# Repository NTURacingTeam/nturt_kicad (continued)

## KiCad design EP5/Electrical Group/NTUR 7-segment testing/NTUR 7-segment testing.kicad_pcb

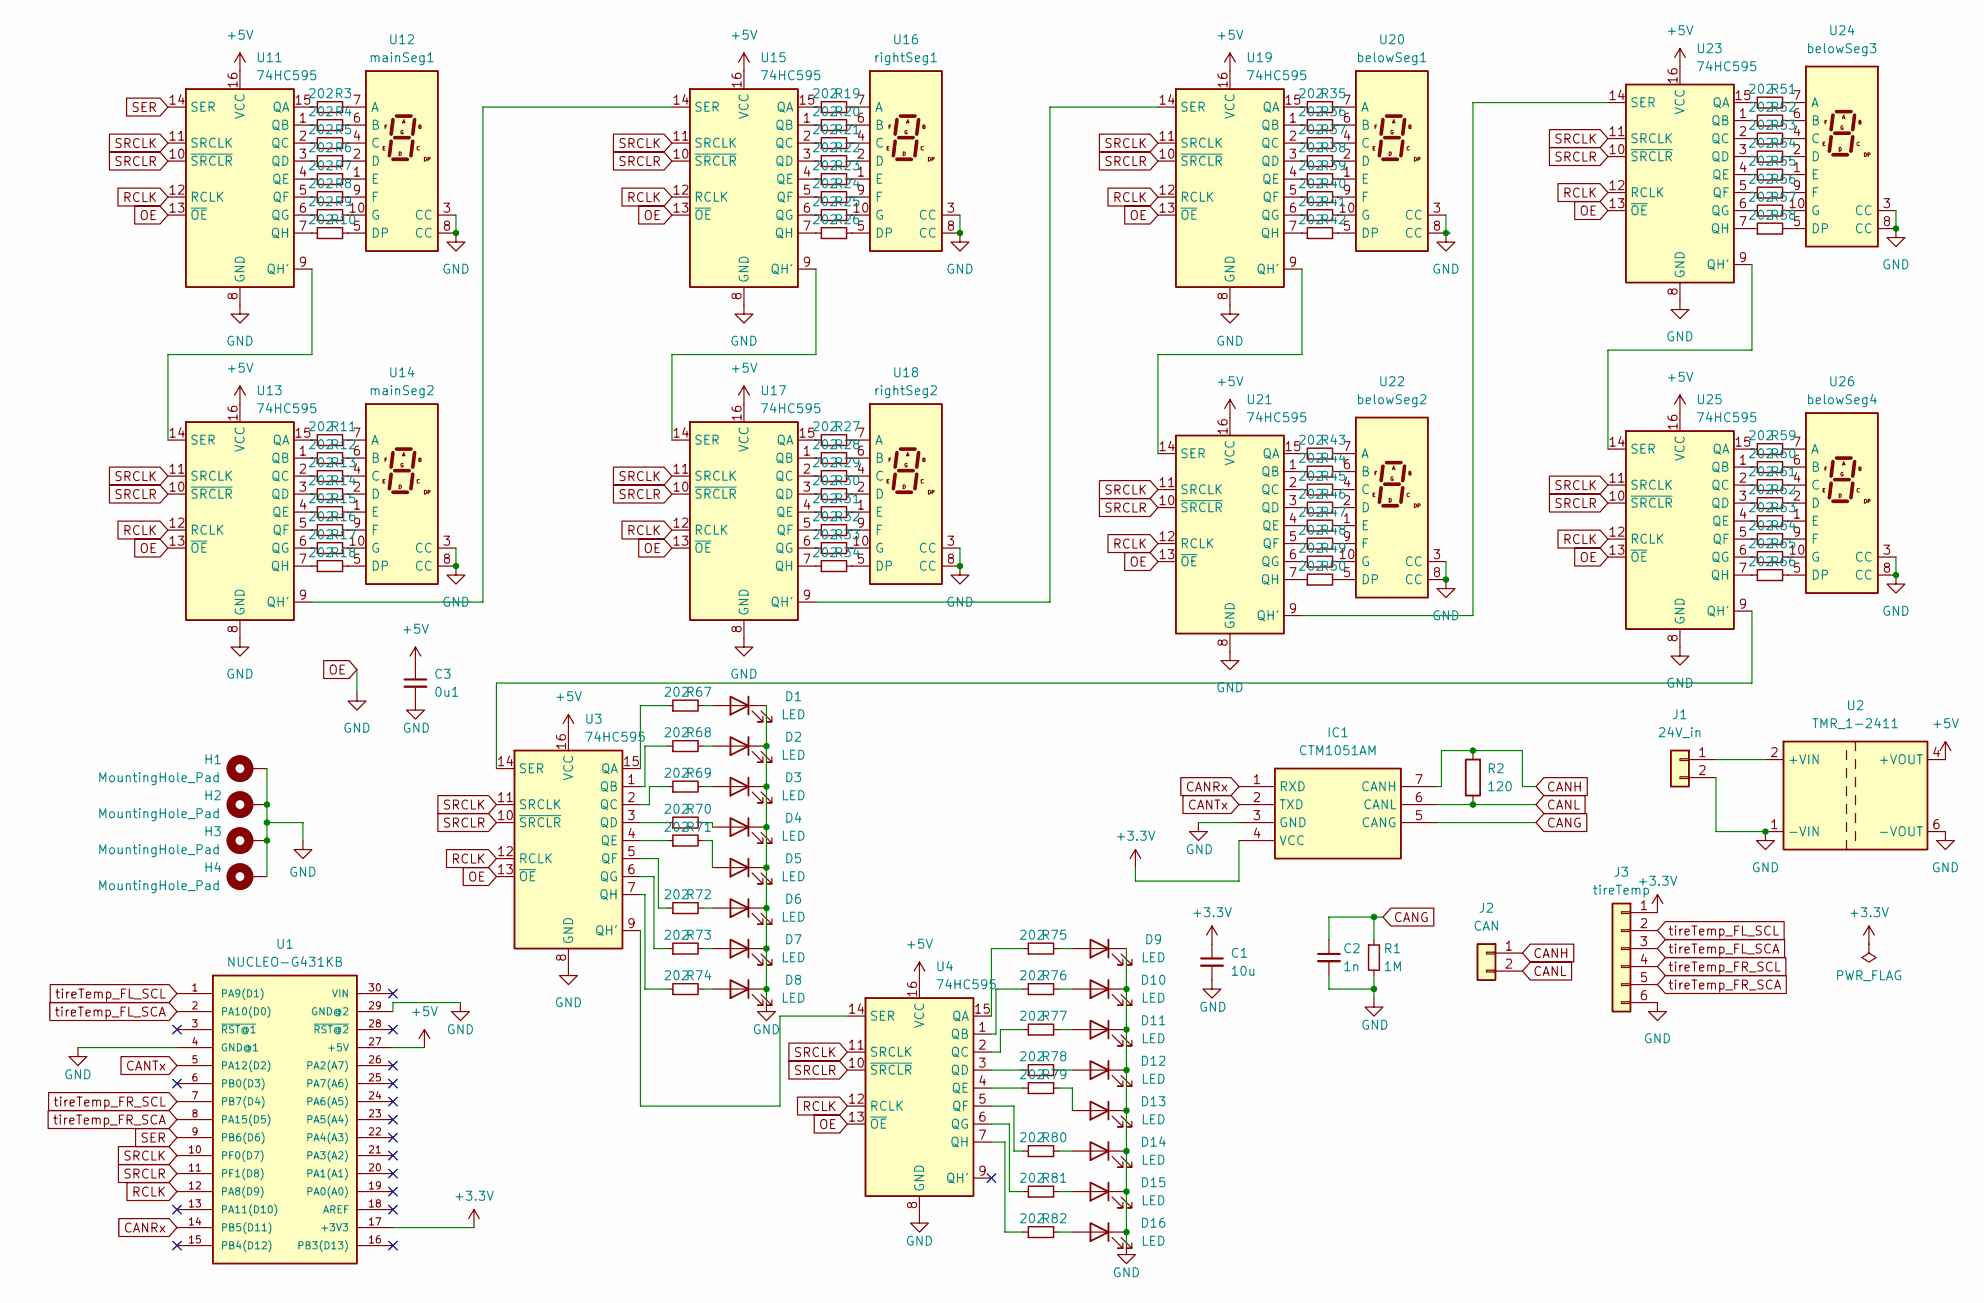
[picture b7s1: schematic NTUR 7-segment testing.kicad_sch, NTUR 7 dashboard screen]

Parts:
C1: 10u; C_0805_2012Metric_Pad1.18x1.45mm_HandSolder
C2: 1n; C_Disc_D5.0mm_W2.5mm_P5.00mm
C3: 0u1; C_0805_2012Metric_Pad1.18x1.45mm_HandSolder
D1, D2, D3, D4, D5, D6, D7, D8, D9, D10, D11, D12, D13, D14, D15, D16: LED; LED_1812_4532Metric
H1, H2, H3, H4: MountingHole_Pad; MountingHole_2.2mm_M2_DIN965_Pad_TopBottom
IC1: CTM1051AM; Manufacturer_Part_Number CTM1051AM
J1: 24V_in; JST_XH_S2B-XH-A-1_1x02_P2.50mm_Horizontal
J2: CAN; JST_XH_S2B-XH-A-1_1x02_P2.50mm_Horizontal
J3: tireTemp; JST_XH_S6B-XH-A-1_1x06_P2.50mm_Horizontal
R1: 1M; R_0603_1608Metric
R2: 120; R_1206_3216Metric
R3, R4, R5, R6, R7, R8, R9, R10, R11, R12, R13, R14, R15, R16, R17, R18, R19, R20, R21, R22, R23, R24, R25, R26, R27, R28, R29, R30, R31, R32, R33, R34, R35, R36, R37, R38, R39, R40, R41, R42, R43, R44, R45, R46, R47, R48, R49, R50, R51, R52, R53, R54, R55, R56, R57, R58, R59, R60, R61, R62, R63, R64, R65, R66, R67, R68, R69, R70, R71, R72, R73, R74, R75, R76, R77, R78, R79, R80, R81, R82: 202; R_0805_2012Metric
U1: NUCLEO-G431KB; MANUFACTURER_PART_NUMBER NUCLEO-F303K8
U2: TMR_1-2411; Converter_DCDC_TRACO_TMR-1-xxxx_Single_THT
U3, U4, U11, U13, U15, U17, U19, U21, U23, U25: 74HC595; DIP-16_W7.62mm_Socket_LongPads
U12: mainSeg1; 1digit 7 segment display 1.5inch
U14: mainSeg2; 1digit 7 segment display 1.5inch
U16: rightSeg1; 1digit 7 segment display 0.56inch
U18: rightSeg2; 1digit 7 segment display 0.56inch
U20: belowSeg1; 1digit 7 segment display 0.56inch
U22: belowSeg2; 1digit 7 segment display 0.56inch
U24: belowSeg3; 1digit 7 segment display 0.56inch
U26: belowSeg4; 1digit 7 segment display 0.56inch

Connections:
+3.3V: C1.1, IC1.4 (VCC), J3.1, U1.17 (+3V3)
+5V: C3.1, U1.27 (+5V), U2.4 (+VOUT), U3.16 (VCC), U4.16 (VCC), U11.16 (VCC), U13.16 (VCC), U15.16 (VCC), U17.16 (VCC), U19.16 (VCC), U21.16 (VCC), U23.16 (VCC), U25.16 (VCC)
CANG: C2.1, IC1.5 (CANG), R1.1
CANH: IC1.7 (CANH), J2.1, R2.2
CANL: IC1.6 (CANL), J2.2, R2.1
CANRx: IC1.1 (RXD), U1.14 (PB5(D11))
CANTx: IC1.2 (TXD), U1.5 (PA12(D2))
unnamed: D1.2 (A), R67.2
unnamed: D2.2 (A), R68.2
unnamed: D3.2 (A), R69.2
unnamed: D4.2 (A), R70.2
unnamed: D5.2 (A), R71.2
unnamed: D6.2 (A), R72.2
unnamed: D7.2 (A), R73.2
unnamed: D8.2 (A), R74.2
unnamed: D9.2 (A), R75.2
unnamed: D10.2 (A), R76.2
unnamed: D11.2 (A), R77.2
unnamed: D12.2 (A), R78.2
unnamed: D13.2 (A), R79.2
unnamed: D14.2 (A), R80.2
unnamed: D15.2 (A), R81.2
unnamed: D16.2 (A), R82.2
unnamed: J1.1, U2.2 (+VIN)
unnamed: R67.1, U3.15 (QA)
unnamed: R68.1, U3.1 (QB)
unnamed: R69.1, U3.2 (QC)
unnamed: R70.1, U3.3 (QD)
unnamed: R71.1, U3.4 (QE)
unnamed: R72.1, U3.5 (QF)
unnamed: R73.1, U3.6 (QG)
unnamed: U3.9 (QH'), U4.14 (SER)
unnamed: R74.1, U3.7 (QH)
unnamed: R75.1, U4.15 (QA)
unnamed: R76.1, U4.1 (QB)
unnamed: R77.1, U4.2 (QC)
unnamed: R78.1, U4.3 (QD)
unnamed: R79.1, U4.4 (QE)
unnamed: R80.1, U4.5 (QF)
unnamed: R81.1, U4.6 (QG)
unnamed: R82.1, U4.7 (QH)
unnamed: R3.1, U11.15 (QA)
unnamed: R4.1, U11.1 (QB)
unnamed: R5.1, U11.2 (QC)
unnamed: R6.1, U11.3 (QD)
unnamed: R7.1, U11.4 (QE)
unnamed: R8.1, U11.5 (QF)
unnamed: R9.1, U11.6 (QG)
unnamed: U11.9 (QH'), U13.14 (SER)
unnamed: R10.1, U11.7 (QH)
unnamed: R3.2, U12.7 (A)
unnamed: R4.2, U12.6 (B)
unnamed: R5.2, U12.4 (C)
unnamed: R6.2, U12.2 (D)
unnamed: R10.2, U12.5 (DP)
unnamed: R7.2, U12.1 (E)
unnamed: R8.2, U12.9 (F)
unnamed: R9.2, U12.10 (G)
unnamed: R11.1, U13.15 (QA)
unnamed: R12.1, U13.1 (QB)
unnamed: R13.1, U13.2 (QC)
unnamed: R14.1, U13.3 (QD)
unnamed: R15.1, U13.4 (QE)
unnamed: R16.1, U13.5 (QF)
unnamed: R17.1, U13.6 (QG)
unnamed: U13.9 (QH'), U15.14 (SER)
unnamed: R18.1, U13.7 (QH)
unnamed: R11.2, U14.7 (A)
unnamed: R12.2, U14.6 (B)
unnamed: R13.2, U14.4 (C)
unnamed: R14.2, U14.2 (D)
unnamed: R18.2, U14.5 (DP)
unnamed: R15.2, U14.1 (E)
unnamed: R16.2, U14.9 (F)
unnamed: R17.2, U14.10 (G)
unnamed: R19.1, U15.15 (QA)
unnamed: R20.1, U15.1 (QB)
unnamed: R21.1, U15.2 (QC)
unnamed: R22.1, U15.3 (QD)
unnamed: R23.1, U15.4 (QE)
unnamed: R24.1, U15.5 (QF)
unnamed: R25.1, U15.6 (QG)
unnamed: U15.9 (QH'), U17.14 (SER)
unnamed: R26.1, U15.7 (QH)
unnamed: R19.2, U16.7 (A)
unnamed: R20.2, U16.6 (B)
unnamed: R21.2, U16.4 (C)
unnamed: R22.2, U16.2 (D)
unnamed: R26.2, U16.5 (DP)
unnamed: R23.2, U16.1 (E)
unnamed: R24.2, U16.9 (F)
unnamed: R25.2, U16.10 (G)
unnamed: R27.1, U17.15 (QA)
unnamed: R28.1, U17.1 (QB)
unnamed: R29.1, U17.2 (QC)
unnamed: R30.1, U17.3 (QD)
unnamed: R31.1, U17.4 (QE)
unnamed: R32.1, U17.5 (QF)
unnamed: R33.1, U17.6 (QG)
unnamed: U17.9 (QH'), U19.14 (SER)
unnamed: R34.1, U17.7 (QH)
unnamed: R27.2, U18.7 (A)
unnamed: R28.2, U18.6 (B)
unnamed: R29.2, U18.4 (C)
unnamed: R30.2, U18.2 (D)
unnamed: R34.2, U18.5 (DP)
unnamed: R31.2, U18.1 (E)
unnamed: R32.2, U18.9 (F)
unnamed: R33.2, U18.10 (G)
unnamed: R35.1, U19.15 (QA)
unnamed: R36.1, U19.1 (QB)
unnamed: R37.1, U19.2 (QC)
unnamed: R38.1, U19.3 (QD)
unnamed: R39.1, U19.4 (QE)
unnamed: R40.1, U19.5 (QF)
unnamed: R41.1, U19.6 (QG)
unnamed: U19.9 (QH'), U21.14 (SER)
unnamed: R42.1, U19.7 (QH)
unnamed: R35.2, U20.7 (A)
unnamed: R36.2, U20.6 (B)
unnamed: R37.2, U20.4 (C)
unnamed: R38.2, U20.2 (D)
unnamed: R42.2, U20.5 (DP)
unnamed: R39.2, U20.1 (E)
unnamed: R40.2, U20.9 (F)
unnamed: R41.2, U20.10 (G)
unnamed: R43.1, U21.15 (QA)
unnamed: R44.1, U21.1 (QB)
unnamed: R45.1, U21.2 (QC)
unnamed: R46.1, U21.3 (QD)
unnamed: R47.1, U21.4 (QE)
unnamed: R48.1, U21.5 (QF)
unnamed: R49.1, U21.6 (QG)
unnamed: U21.9 (QH'), U23.14 (SER)
unnamed: R50.1, U21.7 (QH)
unnamed: R43.2, U22.7 (A)
unnamed: R44.2, U22.6 (B)
unnamed: R45.2, U22.4 (C)
unnamed: R46.2, U22.2 (D)
unnamed: R50.2, U22.5 (DP)
unnamed: R47.2, U22.1 (E)
unnamed: R48.2, U22.9 (F)
unnamed: R49.2, U22.10 (G)
unnamed: R51.1, U23.15 (QA)
unnamed: R52.1, U23.1 (QB)
unnamed: R53.1, U23.2 (QC)
unnamed: R54.1, U23.3 (QD)
unnamed: R55.1, U23.4 (QE)
unnamed: R56.1, U23.5 (QF)
unnamed: R57.1, U23.6 (QG)
unnamed: U23.9 (QH'), U25.14 (SER)
unnamed: R58.1, U23.7 (QH)
unnamed: R51.2, U24.7 (A)
unnamed: R52.2, U24.6 (B)
unnamed: R53.2, U24.4 (C)
unnamed: R54.2, U24.2 (D)
unnamed: R58.2, U24.5 (DP)
unnamed: R55.2, U24.1 (E)
unnamed: R56.2, U24.9 (F)
unnamed: R57.2, U24.10 (G)
unnamed: R59.1, U25.15 (QA)
unnamed: R60.1, U25.1 (QB)
unnamed: R61.1, U25.2 (QC)
unnamed: R62.1, U25.3 (QD)
unnamed: R63.1, U25.4 (QE)
unnamed: R64.1, U25.5 (QF)
unnamed: R65.1, U25.6 (QG)
unnamed: U3.14 (SER), U25.9 (QH')
unnamed: R66.1, U25.7 (QH)
unnamed: R59.2, U26.7 (A)
unnamed: R60.2, U26.6 (B)
unnamed: R61.2, U26.4 (C)
unnamed: R62.2, U26.2 (D)
unnamed: R66.2, U26.5 (DP)
unnamed: R63.2, U26.1 (E)
unnamed: R64.2, U26.9 (F)
unnamed: R65.2, U26.10 (G)
OE: C1.2, C2.2, C3.2, D1.1 (K), D2.1 (K), D3.1 (K), D4.1 (K), D5.1 (K), D6.1 (K), D7.1 (K), D8.1 (K), D9.1 (K), D10.1 (K), D11.1 (K), D12.1 (K), D13.1 (K), D14.1 (K), D15.1 (K), D16.1 (K), H1.1, H2.1, H3.1, H4.1, IC1.3 (GND), J1.2, J3.6, R1.2, U1.4 (GND@1), U1.29 (GND@2), U2.1 (-VIN), U2.6 (-VOUT), U3.8 (GND), U3.13 (~OE), U4.8 (GND), U4.13 (~OE), U11.8 (GND), U11.13 (~OE), U12.3 (CC), U12.8 (CC), U13.8 (GND), U13.13 (~OE), U14.3 (CC), U14.8 (CC), U15.8 (GND), U15.13 (~OE), U16.3 (CC), U16.8 (CC), U17.8 (GND), U17.13 (~OE), U18.3 (CC), U18.8 (CC), U19.8 (GND), U19.13 (~OE), U20.3 (CC), U20.8 (CC), U21.8 (GND), U21.13 (~OE), U22.3 (CC), U22.8 (CC), U23.8 (GND), U23.13 (~OE), U24.3 (CC), U24.8 (CC), U25.8 (GND), U25.13 (~OE), U26.3 (CC), U26.8 (CC)
RCLK: U1.12 (PA8(D9)), U3.12 (RCLK), U4.12 (RCLK), U11.12 (RCLK), U13.12 (RCLK), U15.12 (RCLK), U17.12 (RCLK), U19.12 (RCLK), U21.12 (RCLK), U23.12 (RCLK), U25.12 (RCLK)
SER: U1.9 (PB6(D6)), U11.14 (SER)
SRCLK: U1.10 (PF0(D7)), U3.11 (SRCLK), U4.11 (SRCLK), U11.11 (SRCLK), U13.11 (SRCLK), U15.11 (SRCLK), U17.11 (SRCLK), U19.11 (SRCLK), U21.11 (SRCLK), U23.11 (SRCLK), U25.11 (SRCLK)
SRCLR: U1.11 (PF1(D8)), U3.10 (~SRCLR), U4.10 (~SRCLR), U11.10 (~SRCLR), U13.10 (~SRCLR), U15.10 (~SRCLR), U17.10 (~SRCLR), U19.10 (~SRCLR), U21.10 (~SRCLR), U23.10 (~SRCLR), U25.10 (~SRCLR)
tireTemp_FL_SCA: J3.3, U1.2 (PA10(D0))
tireTemp_FL_SCL: J3.2, U1.1 (PA9(D1))
tireTemp_FR_SCA: J3.5, U1.8 (PA15(D5))
tireTemp_FR_SCL: J3.4, U1.7 (PB7(D4))

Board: 2 copper layers, 129 parts (25 on the bottom side), 186 nets, no tracks yet.

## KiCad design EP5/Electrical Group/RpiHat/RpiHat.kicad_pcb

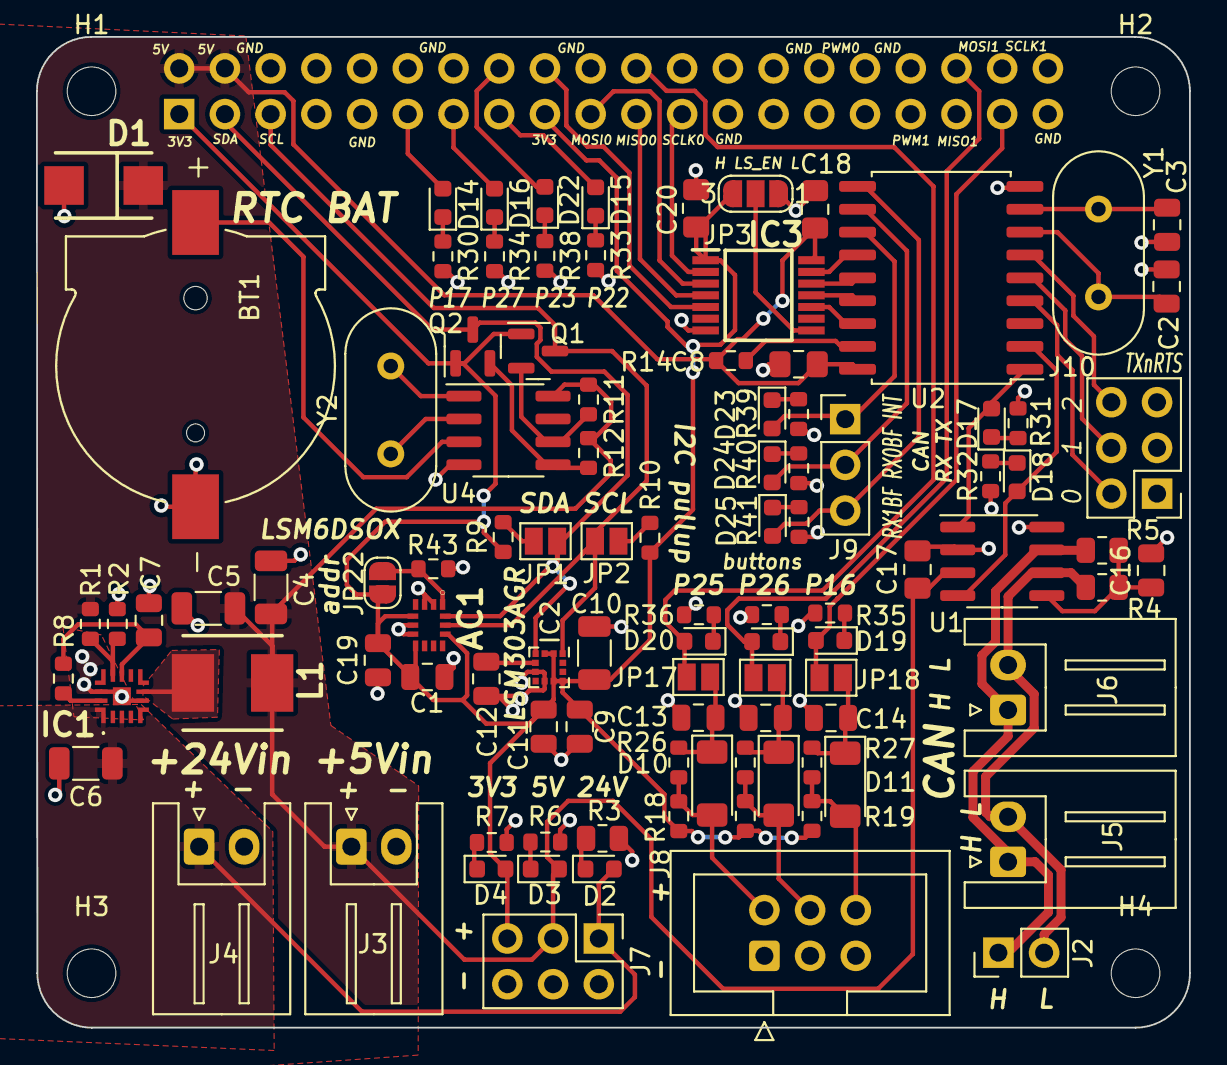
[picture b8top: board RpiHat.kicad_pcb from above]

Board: 2 copper layers, 64.1 x 55.0 mm, 105 parts (1 on the bottom side), 71 nets.

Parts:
AC1: LSM6DSOXTR; LGA-14_1
BT1: RTC battery; BAT_1056
C1, C9, C11, C19: 0u1; C_0805_2012Metric
C2, C3: 30p; C_0805_2012Metric
C4, C5: 22u 16V; C_1206_3216Metric
C6: 10u 35V; C_1206_3216Metric
C7: 1u 16V; C_0805_2012Metric
C8, C17, C18, C20: 0u1; C_0805_2012Metric_Pad1.18x1.45mm_HandSolder
C10: 10u; C_1206_3216Metric
C12: 220n; C_0805_2012Metric
C13, C14, C15: 220p; C_0805_2012Metric
C16: 4n7; C_0805_2012Metric
D1: SMBJ5.0A-TR; SMBJ12A
D2: 24VGood; LED_0603_1608Metric
D3: 5VGood; LED_0603_1608Metric
D4: 3V3Good; LED_0603_1608Metric
D10, D11, D12: 1N4007; D_MiniMELF
D13: P16; LED_0603_1608Metric
D14: P17; LED_0603_1608Metric
D15: P22; LED_0603_1608Metric
D16: P27; LED_0603_1608Metric
D17: CANTX; LED_0603_1608Metric
D18: CANRX; LED_0603_1608Metric
D19: P26; LED_0603_1608Metric
D20: P25; LED_0603_1608Metric
D22: P23; LED_0603_1608Metric
D23: INT; LED_0603_1608Metric
D24: RX0BF; LED_0603_1608Metric
D25: RX1BF; LED_0603_1608Metric
H1, H2, H3, H4: MountingHole; MountingHole_2.7mm_M2.5
IC1: LMQ66420MC5RXBRQ1; LMR66430R5RXBR
IC2: LSM303AGRTR; LGA-12_2x2mm_P0.5mm
IC3: LSF0204DPWR; SOP65P640X120-14N
J1: Raspberry_Pi_2_3; PinSocket_2x20_P2.54mm_Vertical
J2: CAN; PinHeader_1x02_P2.54mm_Vertical
J3: 5Vin; JST_XH_S2B-XH-A_1x02_P2.50mm_Horizontal
J4: 24Vin; JST_XH_S2B-XH-A_1x02_P2.50mm_Horizontal
J5, J6: CAN; JST_XH_S2B-XH-A_1x02_P2.50mm_Horizontal
J7: testPower; PinHeader_2x03_P2.54mm_Vertical
J8: buttons; IDC-Header_2x03_P2.54mm_Vertical
J9: MCP2515out; PinHeader_1x03_P2.54mm_Vertical
J10: Conn_02x03_Odd_Even; PinHeader_2x03_P2.54mm_Vertical
JP1, JP2: I2C_pullup; SolderJumper-2_P1.3mm_Open_Pad1.0x1.5mm
JP3: enable; SolderJumper-3_P1.3mm_Open_RoundedPad1.0x1.5mm_NumberLabels
JP17: button25; SolderJumper-2_P1.3mm_Open_Pad1.0x1.5mm
JP18: button26; SolderJumper-2_P1.3mm_Open_Pad1.0x1.5mm
JP19: button16; SolderJumper-2_P1.3mm_Open_Pad1.0x1.5mm
JP22: LSM6D_addr; SolderJumper-2_P1.3mm_Open_RoundedPad1.0x1.5mm
L1: 4u7 3A; INDPM5552X300N
Q1, Q2: 2N7002; SOT-23
R1: 49k9; R_0603_1608Metric
R2: 12k4; R_0603_1608Metric
R3: 2k2; R_0805_2012Metric
R4, R5: 60R; R_0805_2012Metric
R6: 220R; R_0603_1608Metric
R7, R29, R30, R31, R32, R33, R34, R35, R36, R38, R39, R40, R41: 150R; R_0603_1608Metric
R8, R14, R43: 10k; R_0603_1608Metric
R9, R10, R11, R12: 3k3; R_0603_1608Metric
R18, R19, R20, R26, R27, R28: 4k7; R_0603_1608Metric
U1: SN65HVD1050D; SOIC-8_3.9x4.9mm_P1.27mm
U2: MCP2515-xSO; SOIC-18W_7.5x11.6mm_P1.27mm
U4: DS1307Z+; SOIC-8_3.9x4.9mm_P1.27mm
Y1: 8MHz; Crystal_HC49-U_Vertical
Y2: 32.768kHz; Crystal_HC49-U_Vertical

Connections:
5V_BOOT: IC1.8 (BOOT_1), IC1.18 (NC_7)
5V_PGood: IC1.14 (PG), R8.1
+3V3: AC1.5 (VDDIO), AC1.8 (VDD), AC1.12 (CS), C1.2, C9.2, C10.2, C11.2, C19.2, C20.1, D4.2 (A), IC2.2 (CS_XL), IC2.3 (CS_MAG), IC2.9 (VDD), IC2.10 (VDD_IO), IC3.1 (VREF_A), J1.1 (3V3), J1.17 (3V3), J7.5, JP3.3 (B), JP22.1 (A), Q1.1 (G), Q2.1 (G), R9.1, R10.1, R18.2, R19.2, R20.2
+5V: C4.1, C5.1, C8.1, C17.1, C18.1, D1.1 (K), D3.2 (A), IC3.14 (VREF_B), J1.2 (5V), J1.4 (5V), J3.1, J7.3, L1.1, R1.1, R11.1, R12.1, R14.2, U1.3 (VCC), U2.18 (VDD), U4.8 (VCC)
+24V: C6.1, D2.2 (A), IC1.1 (EN_1), IC1.3 (VIN), IC1.16 (NC_6), J4.1, J7.1
/CANRX: D18.2 (A), U1.4 (RXD), U2.2 (RXCAN)
/CANTX: D17.2 (A), U1.1 (TXD), U2.1 (TXCAN)
/CAN_VREF: C16.1, R4.1, R5.2, U1.5 (VREF)
/GPIOs/Button16: C15.1, D12.1 (K), JP19.1 (A), R28.2
/GPIOs/Button16_raw: D12.2 (A), J8.4, R20.1, R28.1
/GPIOs/Button25: C13.1, D10.1 (K), JP17.1 (A), R26.2
/GPIOs/Button25_raw: D10.2 (A), J8.2, R18.1, R26.1
/GPIOs/Button26: C14.1, D11.1 (K), JP18.1 (A), R27.2
/GPIOs/Button26_raw: D11.2 (A), J8.6, R19.1, R27.1
/INT: D23.2 (A), J9.1, U2.12 (~INT)
/LSM303_C1: C12.2, IC2.5 (C1)
/MCP2515_CS: IC3.10 (B4), U2.16 (~CS)
/MCP2515_MISO: IC3.11 (B3), U2.15 (SO)
/MCP2515_MOSI: IC3.12 (B2), U2.14 (SI)
/MCP2515_SCK: IC3.13 (B1), U2.13 (SCK)
/OSC1: C3.1, U2.8 (OSC1), Y1.1
/OSC2: C2.1, U2.7 (OSC2), Y1.2
/RTC_SCL: Q1.2 (S), R11.2, U4.6 (SCL)
/RTC_SDA: Q2.2 (S), R12.2, U4.5 (SDA)
/RX0BF: D24.2 (A), J9.2, U2.11 (~RX0BF)
/RX1BF: D25.2 (A), J9.3, U2.10 (~RX1BF)
/TX0RTS: J10.2, U2.4 (~TX0RTS)
/TX1RTS: J10.4, U2.5 (~TX1RTS)
/TX2RTS: J10.6, U2.6 (~TX2RTS)
/levelShiftEnable: IC3.8 (EN), JP3.2 (C)
/power/5V_SW: IC1.7 (SW), L1.2
/power/5Vraw: IC1.11 (VOUT/FB), R1.2, R2.1
CANH: J2.1, J5.1, J6.1, R4.2, U1.7 (CANH)
CANL: J2.2, J5.2, J6.2, R5.1, U1.6 (CANL)
GND: AC1.2 (SDX), AC1.3 (SCX), AC1.6 (GND_1), AC1.7 (GND_2), BT1.N, C1.1, C2.2, C3.2, C4.2, C5.2, C6.2, C7.2, C8.2, C9.1, C10.1, C11.1, C12.1, C13.2, C14.2, C15.2, C16.2, C17.2, C18.2, C19.1, C20.2, D1.2 (A), IC1.6 (PGND), IC1.13 (MODE/SYNC), IC1.15 (GND/DAP), IC2.6 (GND_1), IC2.8 (GND_2), IC3.7 (GND), J1.6 (GND), J1.9 (GND), J1.14 (GND), J1.20 (GND), J1.25 (GND), J1.30 (GND), J1.34 (GND), J1.39 (GND), J3.2, J4.2, J7.2, J7.4, J7.6, J8.1, J8.3, J8.5, J10.1, J10.3, J10.5, JP3.1 (A), R2.2, R3.2, R6.2, R7.2, R29.2, R30.2, R31.2, R32.2, R33.2, R34.2, R35.2, R36.2, R38.2, R39.2, R40.2, R41.2, R43.1, U1.2 (GND), U1.8 (S), U2.9 (VSS), U4.4 (GND)
MISO0: IC3.4 (A3), J1.21 (MISO0/GPIO9)
MOSI0: IC3.3 (A2), J1.19 (MOSI0/GPIO10)
unnamed: AC1.1 (SDO/SA0), JP22.2 (B), R43.2
unnamed: D2.1 (K), R3.1
unnamed: D3.1 (K), R6.1
unnamed: D4.1 (K), R7.1
unnamed: D13.1 (K), R29.1
unnamed: D14.1 (K), R30.1
unnamed: D15.1 (K), R33.1
unnamed: D16.1 (K), R34.1
unnamed: D17.1 (K), R31.1
unnamed: D18.1 (K), R32.1
unnamed: D19.1 (K), R35.1
unnamed: D20.1 (K), R36.1
unnamed: D22.1 (K), R38.1
unnamed: D23.1 (K), R39.1
unnamed: D24.1 (K), R40.1
unnamed: D25.1 (K), R41.1
unnamed: C7.1, IC1.10 (VCC), R8.2
unnamed: JP1.1 (A), R9.2
unnamed: JP2.1 (A), R10.2
unnamed: R14.1, U2.17 (~RESET)
unnamed: U4.1 (X1), Y2.2
unnamed: U4.2 (X2), Y2.1
P16: D13.2 (A), J1.36 (GPIO16), JP19.2 (B)
P17: D14.2 (A), J1.11 (GPIO17)
P22: D15.2 (A), J1.15 (GPIO22)
P23: D22.2 (A), J1.16 (GPIO23)
P24: IC3.5 (A4), J1.18 (GPIO24)
P25: D20.2 (A), J1.22 (GPIO25), JP17.2 (B)
P26: D19.2 (A), J1.37 (GPIO26), JP18.2 (B)
P27: D16.2 (A), J1.13 (GPIO27)
RTCbattery: BT1.P, U4.3 (VBAT)
SCL: AC1.13 (SCL), IC2.1 (SCL/SPC), J1.5 (SCL/GPIO3), JP2.2 (B), Q1.3 (D)
SCLK0: IC3.2 (A1), J1.23 (SCLK0/GPIO11)
SDA: AC1.14 (SDA), IC2.4 (SDA/SDI/SDO), J1.3 (SDA/GPIO2), JP1.2 (B), Q2.3 (D)
